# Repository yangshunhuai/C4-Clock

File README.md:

# C4 Clock
自制能爆炸的C4闹钟，再也不怕闹钟叫不醒了（不是

## 介绍
普通的闹钟是叫不醒我这种睡着了就叫不醒的人的，即便声音再响也没用。但是，最近收到了一个新的闹钟，响起来非常像定时炸弹。想到游戏CS:GO里面有一个C4炸弹，可以以它为原型，制作一个C4形状的闹钟，响的时候也像C4那样，就可以很轻易地叫醒人了。

1. 当闹钟响起来之后，必须在30秒内按下键盘上的确认键，否则炸弹里的一个电解电容就会爆炸（当然放个小烟花也是可以的，但是上海弄不到烟花，并且这样的话壳子就不能重复利用了）。
2. 然后屏幕上会有5道数学计算题，每一题15秒，超过时间会爆炸。

## 硬件
MCU采用了乐鑫ESP32-WROOM-32D，支持WiFi+蓝牙，可以自动同步时间，支持通过web端设置闹钟。

PCB文件放在Hardware文件夹下。
> 原理图的J4处是一个直流升压模块，淘宝上有卖的，可以在[这里](https://detail.tmall.com/item.htm?id=41345069371)买到
> 
> 规格如下：
> 
>
> 安装的时候，主板上有对应的四个焊盘，直接一大坨锡糊在四个焊盘上，反正能连上就行了。

## 软件
鉴于Arduino自己的IDE功能太少，不能自动补全也不能单步调试~~我要这废物有何用~~所以想办法弄了一个VS插件（visual micro），可以支持arduino

## 灵感
芜狐ー起飞@bilibili的[计算练习器](https://www.bilibili.com/video/BV1YU4y1j7n4)

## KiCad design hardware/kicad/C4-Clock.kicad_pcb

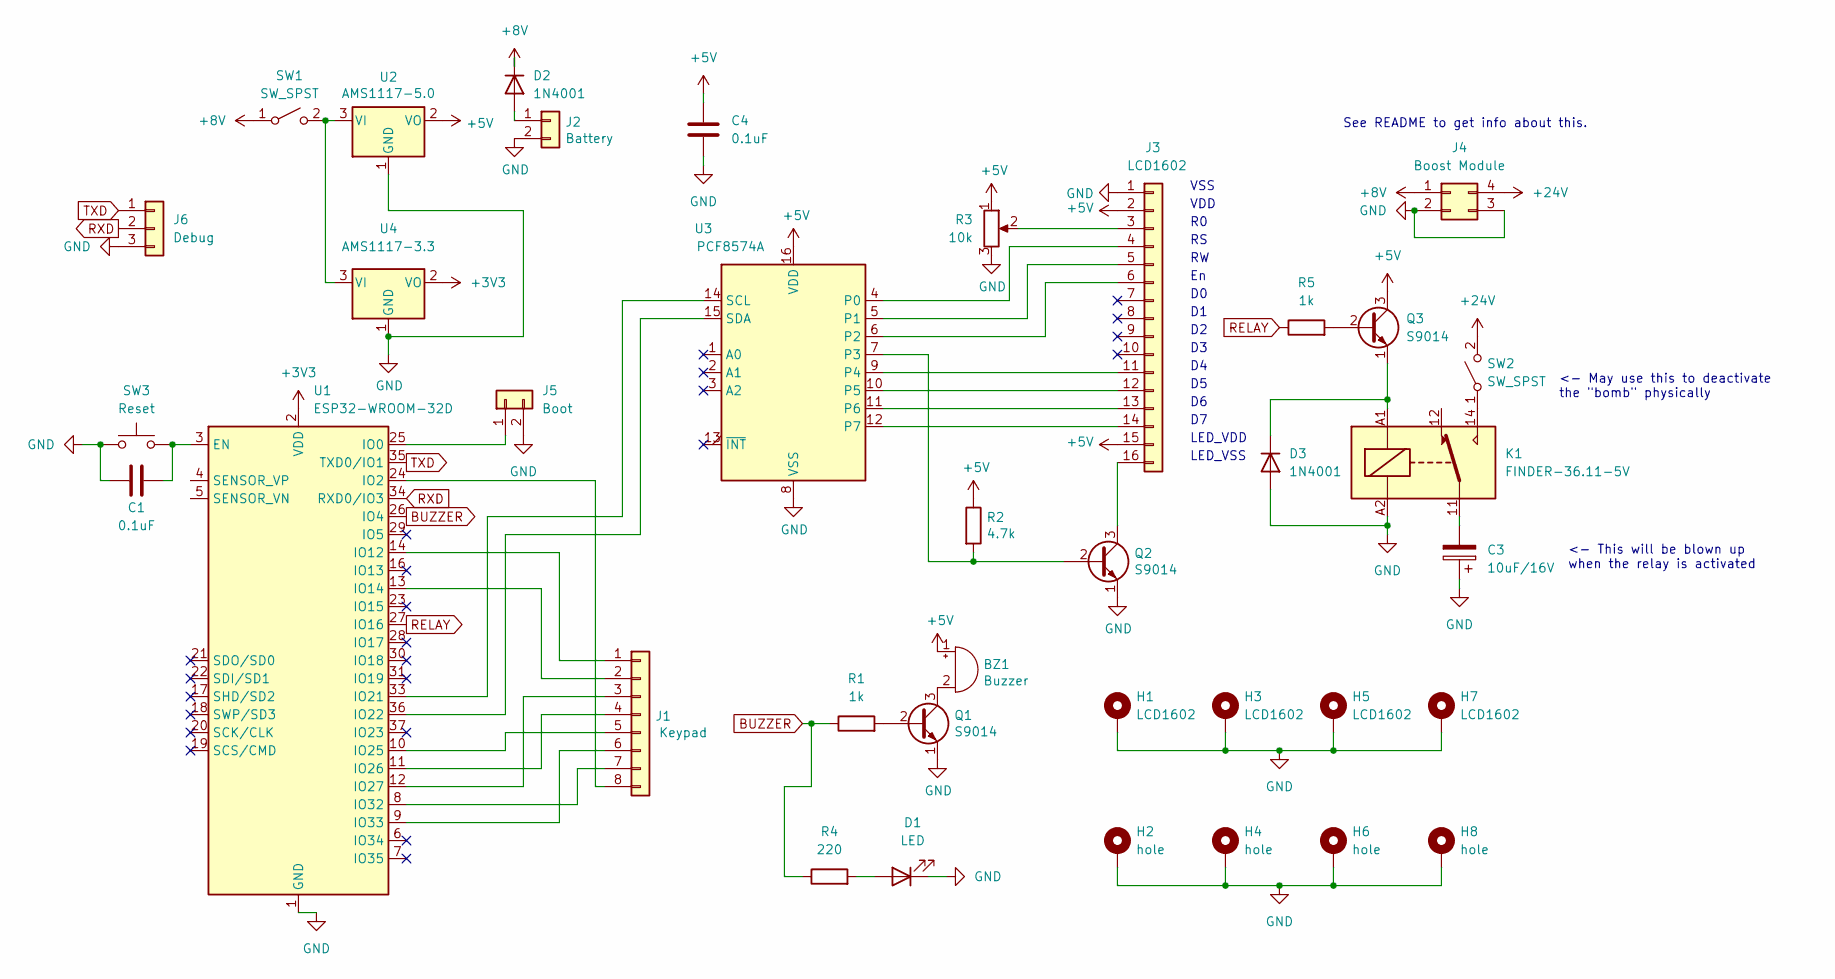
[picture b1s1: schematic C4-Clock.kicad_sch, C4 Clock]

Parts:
BZ1: Buzzer; Buzzer_12x9.5RM7.6
C1, C4: 0.1uF; C_Disc_D4.3mm_W1.9mm_P5.00mm
C3: 10uF/16V; PinSocket_1x02_P2.54mm_Vertical
D1: LED; LED_D5.0mm
D2, D3: 1N4001; D_DO-41_SOD81_P10.16mm_Horizontal
H1, H3, H5, H7: LCD1602; MountingHole_3mm_Pad_TopBottom
H2, H4, H6, H8: hole; MountingHole_3mm_Pad_TopBottom
J1: Keypad; PinHeader_1x08_P2.54mm_Vertical
J2: Battery; PinHeader_1x02_P2.54mm_Horizontal
J3: LCD1602; PinSocket_1x16_P2.54mm_Vertical
J4: Boost Module; DC-Buck-2A
J5: Boot; PinHeader_1x02_P2.54mm_Vertical
J6: Debug; PinHeader_1x03_P2.54mm_Vertical
K1: FINDER-36.11-5V; Relay_SPDT_Finder_36.11
Q1, Q2, Q3: S9014; TO-92
R1, R5: 1k; R_Axial_DIN0207_L6.3mm_D2.5mm_P10.16mm_Horizontal
R2: 4.7k; R_Axial_DIN0207_L6.3mm_D2.5mm_P10.16mm_Horizontal
R3: 10k; Potentiometer_Vishay_T73YP_Vertical
R4: 220; R_Axial_DIN0207_L6.3mm_D2.5mm_P10.16mm_Horizontal
SW1: SW_SPST; SW_E-Switch_EG1271_DPDT
SW2: SW_SPST; SW_Push_2P2T_Toggle_CK_PVA2xxH1xxxxxxV2
SW3: Reset; SW_PUSH_6mm_H5mm
U1: ESP32-WROOM-32D; ESP32-WROOM-32
U2: AMS1117-5.0; SOT-223-3_TabPin2
U3: PCF8574A; DIP-16_W7.62mm_Socket
U4: AMS1117-3.3; SOT-223-3_TabPin2

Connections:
+3V3: U1.2 (VDD), U4.2 (VO)
+5V: BZ1.1 (-), C4.1, J3.2, J3.15, Q3.3 (C), R2.1, R3.1, U2.2 (VO), U3.16 (VDD)
+8V: D2.1 (K), J4.1, SW1.1 (A)
+24V: J4.4, SW2.2 (B)
BUZZER: R1.1, R4.1, U1.26 (IO4)
GND: C1.1, C3.1, C4.2, D1.1 (K), D3.2 (A), H1.1, H2.1, H3.1, H4.1, H5.1, H6.1, H7.1, H8.1, J2.2, J3.1, J4.2, J4.3, J5.2, J6.3, K1.A2, Q1.1 (E), Q2.1 (E), R3.3, SW3.1, U1.1 (GND), U1.15 (GND), U1.38 (GND), U1.39 (GND), U2.1 (GND), U3.8 (VSS), U4.1 (GND)
unnamed: BZ1.2 (+), Q1.3 (C)
unnamed: C1.2, SW3.2, U1.3 (EN)
unnamed: C3.2, K1.11
unnamed: D1.2 (A), R4.2
unnamed: D2.2 (A), J2.1
unnamed: D3.1 (K), K1.A1, Q3.1 (E)
unnamed: J1.1, U1.14 (IO12)
unnamed: J1.2, U1.13 (IO14)
unnamed: J1.3, U1.12 (IO27)
unnamed: J1.4, U1.11 (IO26)
unnamed: J1.5, U1.10 (IO25)
unnamed: J1.6, U1.9 (IO33)
unnamed: J1.7, U1.8 (IO32)
unnamed: J1.8, U1.24 (IO2)
unnamed: J3.3, R3.2
unnamed: J3.4, U3.4 (P0)
unnamed: J3.5, U3.5 (P1)
unnamed: J3.6, U3.6 (P2)
unnamed: J3.11, U3.9 (P4)
unnamed: J3.12, U3.10 (P5)
unnamed: J3.13, U3.11 (P6)
unnamed: J3.14, U3.12 (P7)
unnamed: J3.16, Q2.3 (C)
unnamed: J5.1, U1.25 (IO0)
unnamed: K1.14, SW2.1 (A)
unnamed: Q1.2 (B), R1.2
unnamed: Q2.2 (B), R2.2, U3.7 (P3)
unnamed: Q3.2 (B), R5.2
unnamed: SW1.2 (B), U2.3 (VI), U4.3 (VI)
unnamed: U1.33 (IO21), U3.14 (SCL)
unnamed: U1.36 (IO22), U3.15 (SDA)
RELAY: R5.1, U1.27 (IO16)
RXD: J6.2, U1.34 (RXD0/IO3)
TXD: J6.1, U1.35 (TXD0/IO1)

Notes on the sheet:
VSS
<- May use this to deactivate the "bomb" physically
VDD
LED_VDD
See README to get info about this.
LED_VSS
<- This will be blown up when the relay is activated

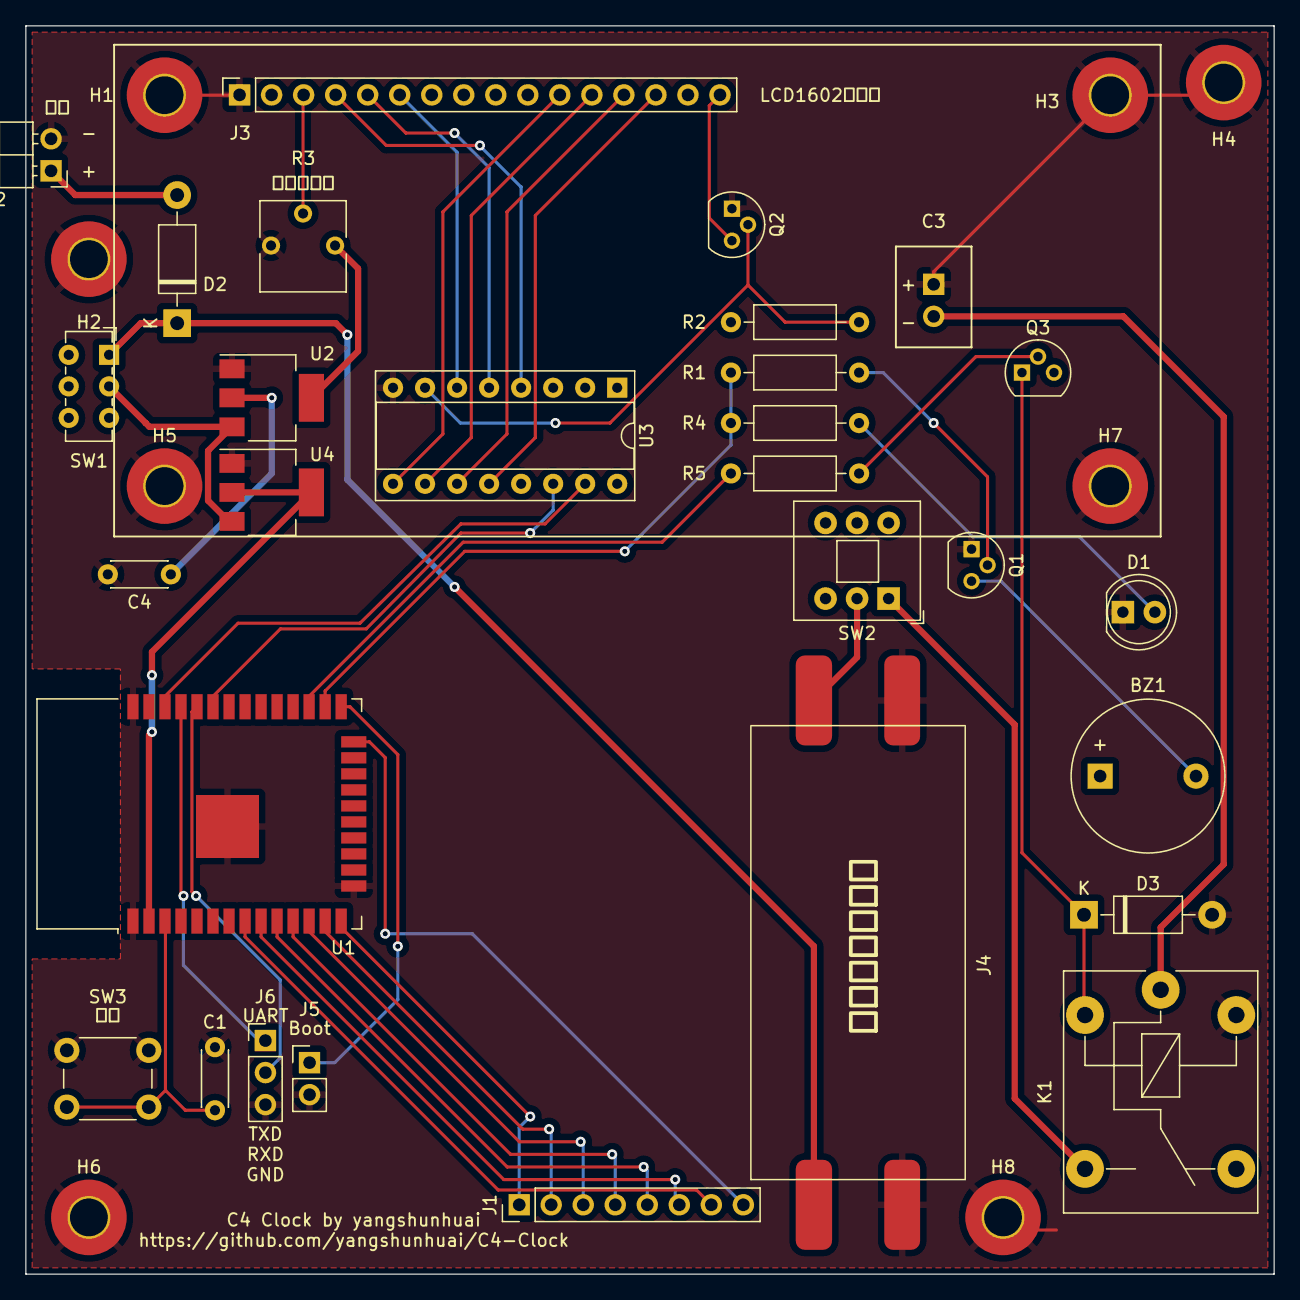
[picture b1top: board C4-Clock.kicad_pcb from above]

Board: 2 copper layers, 99.0 x 99.0 mm, 37 parts (1 on the bottom side), 40 nets.

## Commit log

2022-04-22 lots of update
2022-04-23 Hardware Update
2022-04-23 Update gitignore
2022-04-28 Update gitignore to ignore KiCad backup files
2022-04-28 3d-model: Add FreeCAD 3D model
2022-04-28 kicad: create PCB
2022-04-29 doc: Add lcd1602 reference
2022-05-04 software: Added VS files
2022-05-04 Removed VS Code files
2022-05-06 software: Add library
2022-05-06 hardware: Add parts
2022-05-08 software: Add initialization and main menu
2022-05-15 hardware: Update PCB
2022-05-15 hardware: Update 3D Model
2022-05-15 software: Add alarm config UI
2022-05-22 3d-model: Added pad for screwholes above
2022-05-22 kicad: prl update
2022-05-22 software: some refactor for PeriphControl and added setTime menu
2022-05-22 Removed all hardware files for directory structure fix
2022-05-22 Added hardware files for directory structure fix
2022-06-25 Set time function completed
2022-06-25 Set alarm function completed
2022-06-25 Restructured reset EEPROM logic
2022-06-25 Fixed unable to turn off alarm bug
2022-06-26 kicad: Remove unused pin A0
2022-07-02 Added Proteus simulation model
2022-07-02 Last update for ATmega branch
2022-07-02 kicad: removed DS1302 and atmega
2022-07-16 kicad: Change ATmega328P to ESP32-WROOM-32
2022-07-17 software: Completely port VS to PlatformIO
2022-07-17 Using Keypad library
2022-07-18 Ignore .pio build files
2022-07-18 software: Using Adafruit_Keypad
